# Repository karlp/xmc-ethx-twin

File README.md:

# Ethercat + Ethernet using the same physical ports

XMC4800 has ethercat ports _separate_ from ethernet, and you're expected to add a third port.

That sounds super dumb.  

I'm not trying to use ethernet and ethercat at the same time, but in an environment without ethercat, or, prior to commissioning, being able to use one of the ports as a plain ethernet port would be "nice"

This board attempts to evaluate whether that is actually possible, by using two MII phys (the ethercat ports only support MII in xmc4800) with one of them, connected in parallel to the ethernet interface.  I'm hoping to be able to just switch IOs off to the "unused" interface, and.... hope the trace stubs are minor enough to not care about...

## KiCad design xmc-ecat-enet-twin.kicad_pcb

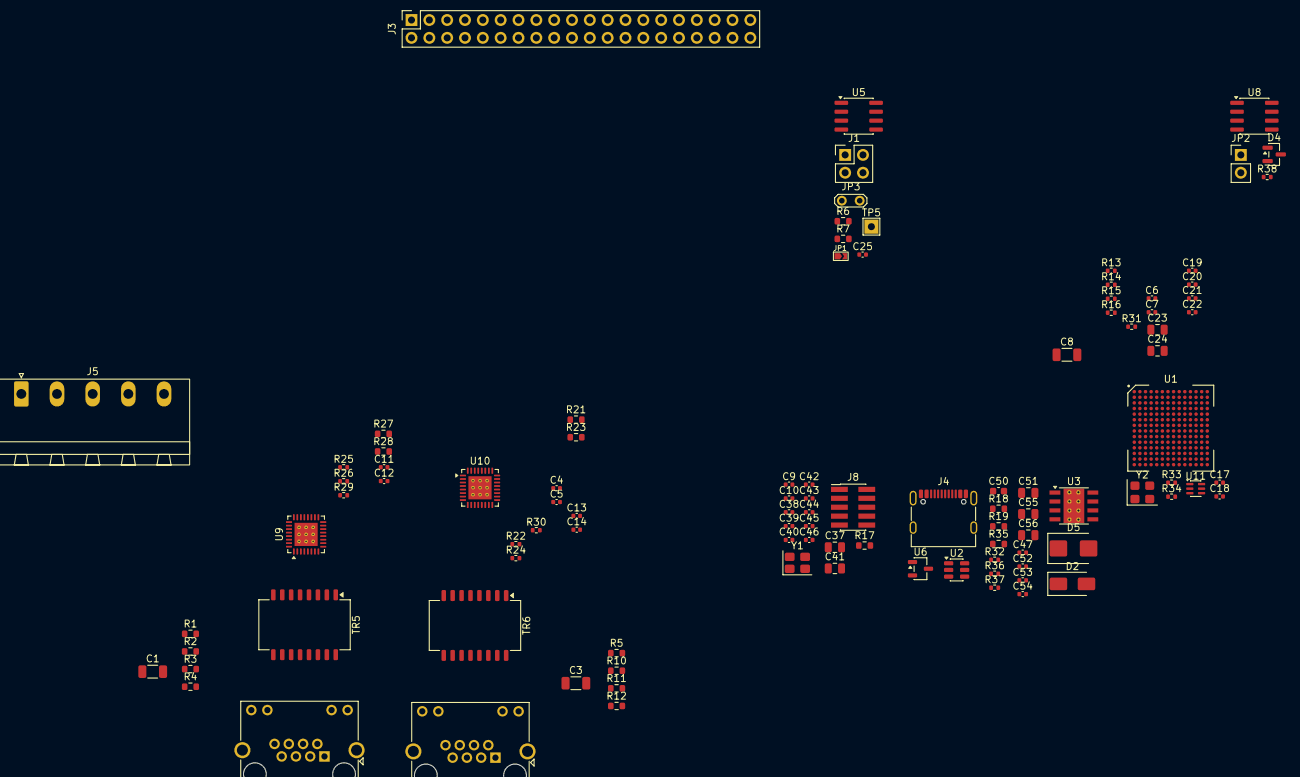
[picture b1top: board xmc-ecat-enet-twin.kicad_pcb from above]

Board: 2 copper layers, 102 parts (0 on the bottom side), 119 nets, no tracks yet.

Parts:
C1, C3, C8: 1nF; C_1206_3216Metric
C4, C5, C6, C7: 10nF; C_0402_1005Metric
C9, C10: 22pF; C_0402_1005Metric
C11, C12, C13, C14, C17, C18, C19, C20, C21, C22, C25, C38, C39, C40, C42, C43, C44, C45, C46, C47: 100nF; C_0402_1005Metric
C23, C24, C37, C41: 10uF; C_0805_2012Metric
C50: 100nF; C_0603_1608Metric
C51, C55, C56: 22uF; C_0805_2012Metric
C52, C53, C54: 1uF; C_0402_1005Metric
D2: Diode_SS34; D_SMA
D4: NUP2105L; SOT-23
D5: TVS_SMBJ33A; D_SMB
J1: Conn_02x02_Counter_Clockwise; PinHeader_2x02_P2.54mm_Vertical
J3: GPIO; PinSocket_2x20_P2.54mm_Vertical
J4: USB_C_Receptacle_USB2.0; USB_C_Receptacle_G-Switch_GT-USB-7010ASV
J5: Conn_01x05; PhoenixContact_MSTBA_2,5_5-G-5,08_1x05_P5.08mm_Horizontal
J6, J7: RJ45_LED_Shielded; RJ45_Amphenol_RJHSE538X
J8: Conn_ARM_JTAG_SWD_10; PinHeader_2x05_P1.27mm_Vertical_SMD
JP1: ID_WP; SolderJumper-2_P1.3mm_Open_TrianglePad0.9x1.8mm
JP2: Jumper_2_Open; PinHeader_1x02_P2.54mm_Vertical
JP3: KJumper_2; TestPoint_2Pads_Pitch2.54mm_Drill0.8mm
R1, R2, R3, R4, R5, R10, R11, R12: 75R; R_0603_1608Metric
R6, R7: 3k9; R_0603_1608Metric
R13, R14, R15, R16, R22, R24, R25, R26, R31, R36, R37: 5k1; R_0402_1005Metric
R17, R18, R19: 0R; R_0603_1608Metric
R21, R23, R27, R28: 510R; R_0603_1608Metric
R29, R30: 2.49k; R_0402_1005Metric
R32: 120k; R_0402_1005Metric
R33, R34, R38: 10k; R_0402_1005Metric
R35: 30k; R_0603_1608Metric
TP5: TestPoint; TestPoint_THTPad_2.0x2.0mm_Drill1.0mm
TR5, TR6: PT61017PEL; Transformer_Ethernet_Bourns_PT61017PEL
U1: XMC4800-E196; LFBGA-196_14x14_P0.8mm
U2: Protection_SRV05-4A; SOT-23-6
U3: LMR33630BDDA; Texas_HSOP-8-1EP_3.9x4.9mm_P1.27mm_ThermalVias
U5: M24c64; SOIC-8_3.9x4.9mm_P1.27mm
U6: XC6206P332MR; SOT-23-3
U8: SN65HVD230; SOIC-8_3.9x4.9mm_P1.27mm
U9, U10: RTL8201F; QFN-32-1EP_5x5mm_P0.5mm_EP3.3x3.3mm_ThermalVias
U11: UMW3157; SOT-363_SC-70-6
Y1: 12M; Crystal_SMD_3225-4Pin_3.2x2.5mm
Y2: Oscillator_25M_3225_3v3_YSO110TR; Oscillator_SMD_3225_YXC_YSO110TR-4Pin_3.2x2.5mm

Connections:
3V3PI: J3.1, J3.17, R19.2
5VPI: J3.2, J3.4, JP3.1 (A), TP5.1 (1_1)
+3V3: C17.1, C18.1, C19.1, C20.1, C21.1, C22.1, C23.1, C24.1, C25.1, C37.1, C38.1, C39.1, C40.1, J8.1 (VTref), JP2.2 (B), R6.1, R7.1, R18.2, R19.1, R24.1, R31.1, R34.1, U1.C11 (VDDP), U1.D1 (VDDP), U1.J1 (VBAT), U1.N12 (VDDP), U5.8 (VCC), U9.7 (VDDA), U9.14 (VDD33), U9.30 (VDDA), U10.7 (VDDA), U10.14 (VDD33), U10.30 (VDDA), U11.5 (V+), Y2.4 (Vdd)
+5V: C51.1, C53.1, C55.1, C56.1, D2.1 (K), JP3.2 (B), R32.1, U6.3 (VI)
+24V: C50.1, D5.1 (K), J5.5, U3.2 (VIN), U3.3 (EN)
/CAN_RX: U1.L9 (P2.6), U8.4 (R)
/CAN_SHUTDOWN: R38.2, U8.8 (Rs)
/CAN_TX: U1.M9 (P2.7), U8.1 (D)
/ECAT_MDC: U1.B11 (P9.6), U1.F12 (P1.10), U9.22 (MDC), U10.22 (MDC)
/ECAT_MDIO: R31.2, U1.A9 (P9.7), U1.F11 (P1.11), U9.23 (MDIO), U10.23 (MDIO)
/ECAT_PHY_25M: U1.G12 (P1.13), U11.3
/ETH.RXD0: U1.K9 (P5.0), U1.N14 (P7.4), U9.9 (RXD0)
/ETH.RXD1: U1.K8 (P5.1), U1.L14 (P7.5), U9.10 (RXD1)
/ETH.RXD2: U1.K6 (P5.8), U1.K14 (P7.6), U9.11 (RXD2/INTB)
/ETH.RXD3: U1.J14 (P7.7), U1.M6 (P5.9), U9.12 (RXD3/CLK_CTL)
/ETH.RX_CLK: U1.G14 (P7.10), U1.H11 (P6.5), U9.13 (RXCLK)
/ETH.RX_DVC: R15.1, U1.F14 (P7.11), U1.K7 (P5.2), U9.8 (RXDV)
/ETH.RX_ERR: R13.1, U1.G13 (P7.9), U1.L10 (P5.3), U9.28 (RXER/FXEN)
/ETH.TXD0: U1.C5 (P0.5), U1.L13 (P7.0), U9.16 (TXD0)
/ETH.TXD1: U1.C6 (P0.6), U1.M13 (P7.1), U9.17 (TXD1)
/ETH.TXD2: U1.J10 (P6.0), U1.N13 (P7.2), U9.18 (TXD2)
/ETH.TXD3: U1.H9 (P6.1), U1.M14 (P7.3), U9.19 (TXD3)
/ETH.TX_CLK: U1.E14 (P9.1), U1.H12 (P6.6), U9.15 (TXCLK)
/ETH.TX_ENA: U1.G11 (P1.12), U1.H14 (P7.8), U9.20 (TXEN)
/ETH_PHY_25M: U11.1, Y2.3 (OUT)
/P1.RXD0: U1.B6 (P8.4), U10.9 (RXD0)
/P1.RXD1: U1.B5 (P8.5), U10.10 (RXD1)
/P1.RXD2: U1.A2 (P8.6), U10.11 (RXD2/INTB)
/P1.RXD3: U1.B4 (P8.7), U10.12 (RXD3/CLK_CTL)
/P1.RX_CLK: U1.A4 (P8.10), U10.13 (RXCLK)
/P1.RX_DVC: R16.1, U1.A6 (P8.11), U10.8 (RXDV)
/P1.RX_ERR: R14.1, U1.A5 (P8.9), U10.28 (RXER/FXEN)
/P1.TXD0: U1.B7 (P8.0), U10.16 (TXD0)
/P1.TXD1: U1.A7 (P8.1), U10.17 (TXD1)
/P1.TXD2: U1.B3 (P8.2), U10.18 (TXD2)
/P1.TXD3: U1.B2 (P8.3), U10.19 (TXD3)
/P1.TX_CLK: U1.F13 (P9.0), U10.15 (TXCLK)
/P1.TX_ENA: U1.A3 (P8.8), U10.20 (TXEN)
/PHY_CLK_SEL: R33.1, U11.6
/PHY_RST_N: U1.D14 (P9.2), U9.21 (~RST), U10.21 (~RST)
/Power/CANH: D4.1 (K), J5.4, U8.7 (CANH)
/Power/CANL: D4.2 (K), J5.2, U8.6 (CANL)
/SC_RX1: J1.4, U1.L6 (P2.15)
/SC_TX1: J1.3, U1.M7 (P2.14)
/SPI_21_CS: J3.24, U1.G8 (P4.2)
/SPI_21_MISO: J3.21, U1.F2 (P3.12)
/SPI_21_MOSI: J3.19, U1.F3 (P3.11)
/SPI_21_SCLK: J3.23, U1.E2 (P3.13)
/can/Local3v3: JP2.1 (A), U8.3 (VCC)
/ether_xx/P1.LED0: J7.9, R21.2, R27.2
/ether_xx/P1.LED1: J7.12, R23.2, R28.2
/ether_xx/PHY_25M: U9.32 (XTAL2/CLKIN), U10.32 (XTAL2/CLKIN), U11.4
/pi_interface/GPIO14/TXD0: J1.1, J3.8
/pi_interface/GPIO15/RXD0: J1.2, J3.10
/pi_interface/ID_SCL: J3.28, R7.2, U5.6 (SCL)
/pi_interface/ID_SDA: J3.27, R6.2, U5.5 (SDA)
CHIP_PU: R17.2, U1.J11 (~PORST)
GND: C1.2, C4.2, C5.2, C6.2, C7.2, C8.1, C9.1, C10.1, C11.2, C12.2, C13.2, C14.2, C17.2, C18.2, C19.2, C20.2, C21.2, C22.2, C23.2, C24.2, C25.2, C37.2, C38.2, C39.2, C40.2, C41.2, C42.2, C43.2, C44.2, C45.2, C46.2, C50.2, C51.2, C52.2, C53.2, C54.2, C55.2, C56.2, D4.3 (A), D5.2 (A), J3.6, J3.9, J3.14, J3.20, J3.25, J3.30, J3.34, J3.39, J4.A1 (GND), J4.A12 (GND), J4.B1 (GND), J4.B12 (GND), J5.1, J5.3, J6.9, J6.11, J6.SH, J7.10, J7.11, J8.3 (GND), J8.5 (GND), J8.9 (GNDDetect), R13.2, R14.2, R15.2, R16.2, R22.2, R25.1, R26.2, R29.2, R30.2, R33.2, R35.2, R36.2, R37.2, R38.1, U1.A1 (VSS), U1.A14 (VSS), U1.B13 (VSS), U1.C1 (VSS), U1.C12 (VSS), U1.L12 (VSSO), U1.P1 (VSSA), U1.P2 (VAGND), U1.P12 (VSS), U1.P14 (VSS), U2.2 (GND), U3.1 (GND), U3.9 (GND), U5.4 (GND), U6.1 (GND), U8.2 (GND), U9.31 (XTAL1), U9.33 (VSS), U10.31 (XTAL1), U10.33 (VSS), U11.2 (GND), Y1.2, Y1.4, Y2.2 (GND)
GNDPWR: C3.2, C8.2, J7.SH
JTAG_TCK: J8.4 (SWCLK/TCK), U1.J8 (TCK)
JTAG_TDO: J8.6 (SWO/TDO), U1.M12 (P2.1)
JTAG_TMS: J8.2 (SWDIO/TMS), U1.J7 (TMS)
unnamed: C1.1, R1.2, R2.2, R3.2, R4.2
unnamed: C3.1, R5.2, R10.2, R11.2, R12.2
unnamed: C41.1, C42.1, C43.1, C44.1, U1.C2 (VDDC), U1.D12 (VDDC), U1.P11 (VDDC)
unnamed: J4.A5 (CC1), R36.1
unnamed: J4.B5 (CC2), R37.1
unnamed: J6.4, J6.5, R3.1
unnamed: J6.7, J6.8, R2.1
unnamed: J7.4, J7.5, R11.1
unnamed: J7.7, J7.8, R12.1
unnamed: J8.10 (~RESET), R17.1
unnamed: C7.1, TR5.7 (C_RD)
unnamed: R1.1, TR5.10 (C_RX)
unnamed: C6.1, TR5.2 (C_TD)
unnamed: R4.1, TR5.15 (C_TX)
unnamed: TR5.6 (RD+), U9.5 (RXP)
unnamed: TR5.8 (RD-), U9.6 (RXN)
unnamed: J6.3, TR5.11 (RX+)
unnamed: J6.6, TR5.9 (RX-)
unnamed: TR5.1 (TD+), U9.3 (TXP)
unnamed: TR5.3 (TD-), U9.4 (TXN)
unnamed: J6.1, TR5.16 (TX+)
unnamed: J6.2, TR5.14 (TX-)
unnamed: C4.1, TR6.7 (C_RD)
unnamed: R5.1, TR6.10 (C_RX)
unnamed: C5.1, TR6.2 (C_TD)
unnamed: R10.1, TR6.15 (C_TX)
unnamed: TR6.6 (RD+), U10.5 (RXP)
unnamed: TR6.8 (RD-), U10.6 (RXN)
unnamed: J7.3, TR6.11 (RX+)
unnamed: J7.6, TR6.9 (RX-)
unnamed: TR6.1 (TD+), U10.3 (TXP)
unnamed: TR6.3 (TD-), U10.4 (TXN)
unnamed: J7.1, TR6.16 (TX+)
unnamed: J7.2, TR6.14 (TX-)
unnamed: C45.1, U1.P3 (VAREF)
unnamed: C46.1, U1.N1 (VDDA)
unnamed: C9.2, U1.K11 (XTAL1), Y1.3
unnamed: C10.2, U1.K12 (XTAL2), Y1.1
unnamed: C47.1, U3.7 (BOOT)
unnamed: R32.2, R35.1, U3.5 (FB)
unnamed: C47.2, U3.8 (SW)
unnamed: C52.1, U3.6 (VCC)
unnamed: C54.1, R18.1, U6.2 (VO)
unnamed: R25.2, R27.1, U9.24 (LED0/PHYADD0/PMEB)
unnamed: R26.1, R28.1, U9.25 (LED1/PHYADD1)
unnamed: R29.1, U9.1 (RSET)
unnamed: C12.1, U9.29 (VDD10OUT)
unnamed: C11.1, U9.2 (VDDA10OUT)
unnamed: R21.1, R24.2, U10.24 (LED0/PHYADD0/PMEB)
unnamed: R22.1, R23.1, U10.25 (LED1/PHYADD1)
unnamed: R30.1, U10.1 (RSET)
unnamed: C14.1, U10.29 (VDD10OUT)
unnamed: C13.1, U10.2 (VDDA10OUT)
unnamed: R34.2, Y2.1 (EN)
USB_DM: J4.A7 (D-), J4.B7 (D-), U1.F1 (USB_DM), U2.3 (I/O2)
USB_DP: J4.A6 (D+), J4.B6 (D+), U1.G1 (USB_DP), U2.4 (I/O3)
VBUS: D2.2 (A), J4.A4 (VBUS), J4.A9 (VBUS), J4.B4 (VBUS), J4.B9 (VBUS), U1.G2 (VBUS), U2.5 (VBUS)

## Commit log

2026-04-17 Initial stub
2026-04-18 notes on ethernet parts
2026-04-18 more pulse transformers
2026-04-19 Add missing file and update .pro
2026-04-19 no idea why the uuids went up by one, but, whatever.
2026-04-19 updates to the pin sheeet
2026-04-20 sketching continues
    You cannot do MII on F100 package, so don't even try on the F144,
    there's no saving vs the E196.
    Start stuffing in what else you'd actually need for this. Give it a pi
    interface to use as a daughterboard, usb to use standalone, jbt marel
    can to use there,
    always underestimate just how much _stuff_ there is to do though...
2026-04-21 finish the tism on magnetics.
    jsut use H110X symbol numbering and any H110x footprint, they're all the
    same.
2026-04-22 ether: switch phys, confirm magnetics, start wiring
    Moved from LAN8710 to RTL8201 for the phys. voltage mode instead of
    current mode so less hassle getting them up, and less parts. Also
    cheaper, and realllly well supported too, so, all good. Had to make a
    symbol, but that's not realllly a big deal right?
    We've locked in the arrangement and footprint for the magnetics now too
    at least, after our research tear on them.
2026-04-24 continue with the phys, add debug, hook more up
2026-04-24 connect the dots!
2026-04-29 push forwards: clock muxing, filling in blanks
    Finished off the ethernet section finally.
    Sorted a solution to the 25M phy clocks required for ethercat
    Connected CAN as per existing hardware (and fixed a bug in speed mode)
    Sorted out bypassing for MCU
    Added more thoughts on the external interfaces
    Started on a 24V supply
2026-04-30 sch: make phy clock default to ethercat
    This makes it possible to run unmodified 816 fw on this. (in theory)
2026-04-30 sch: clean up layout a little
    just make it prettier
2026-04-30 spreadsheet isn't just for pins
2026-05-02 finish a 24V supply
    went with a more modern one, plenty of room. Should be pretty good now.
    Went over and filled in a bunch of missing parts and things, cleaned up
    as much as I could 0603 vs 0402 for most, updated some thigns to current
    atomic part library.
    still to go, the "pi" interface and some sort of spi/io interface?
2026-05-02 connect spi and uart to pi interface
    we'll even have jumpers for being the hat or the baseboard for uart...
    need to re-open modus to find new pins for i2c...
2026-05-02 start pcb?
    already twisted to hell. must be another choice for phy routing...
